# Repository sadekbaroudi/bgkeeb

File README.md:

# Pronunciation

Baby Groot Keyboard (bgkeeb)

This is a reversible 100mm x 100mm pcb with support for mx or choc switches (no hotswap), per key led, rotary encoders, and exposes the SDA/SCL/GND/VCC lines in the form of the pimoroni trackball pins (meaning you can add that as well, though the case doesn't support it, so you'll need to devise your own mechanism).

Given the pcb is so small, pcb prototype manufacturers will fab this for very cheap, or even free. As of this writing, nextpcb will ship fab and ship this keyboard 100% for free (in green only). jlcpcb will fab and ship these for $2 (USD).

# PCBs

There are two pcbs, the choc version and the mx version.

For the mx version, see the pcb/mx directory in the repository
For the choc version, see the pcb/mx directory in the repository

# Support me!

I have spent a lot of time and money designing prototypes, testing, developing, etc. Any contributions would be greatly appreciated!

If you don't want to, or can't afford to support me, please send me a message to let me know you've built one, along with pictures. Also, feel free to submit a pull request with pictures into this repository. I'd be happy to showcase your build.

Reddit: /u/sadekbaroudi
Discord: sadekbaroudi#1258

# Firmware

You can use the firmware found here:
https://github.com/sadekbaroudi/qmk_firmware/tree/master/keyboards/fingerpunch/bgkeeb/

zmk firmware here: https://github.com/ezxzeng/zmk-bgkeeb

# Pictures

# Submitted build pics

@ardakilic

@carboncopy101

@robopuff

@JulioPDX

@ezxzeng

case for the wireless choc build found [here](https://cad.onshape.com/documents/f9433f7cbaacd819773968dc/w/7cd753696df5795c5e7db3c3/e/7a6c60eb671b22fb31dd6c76)

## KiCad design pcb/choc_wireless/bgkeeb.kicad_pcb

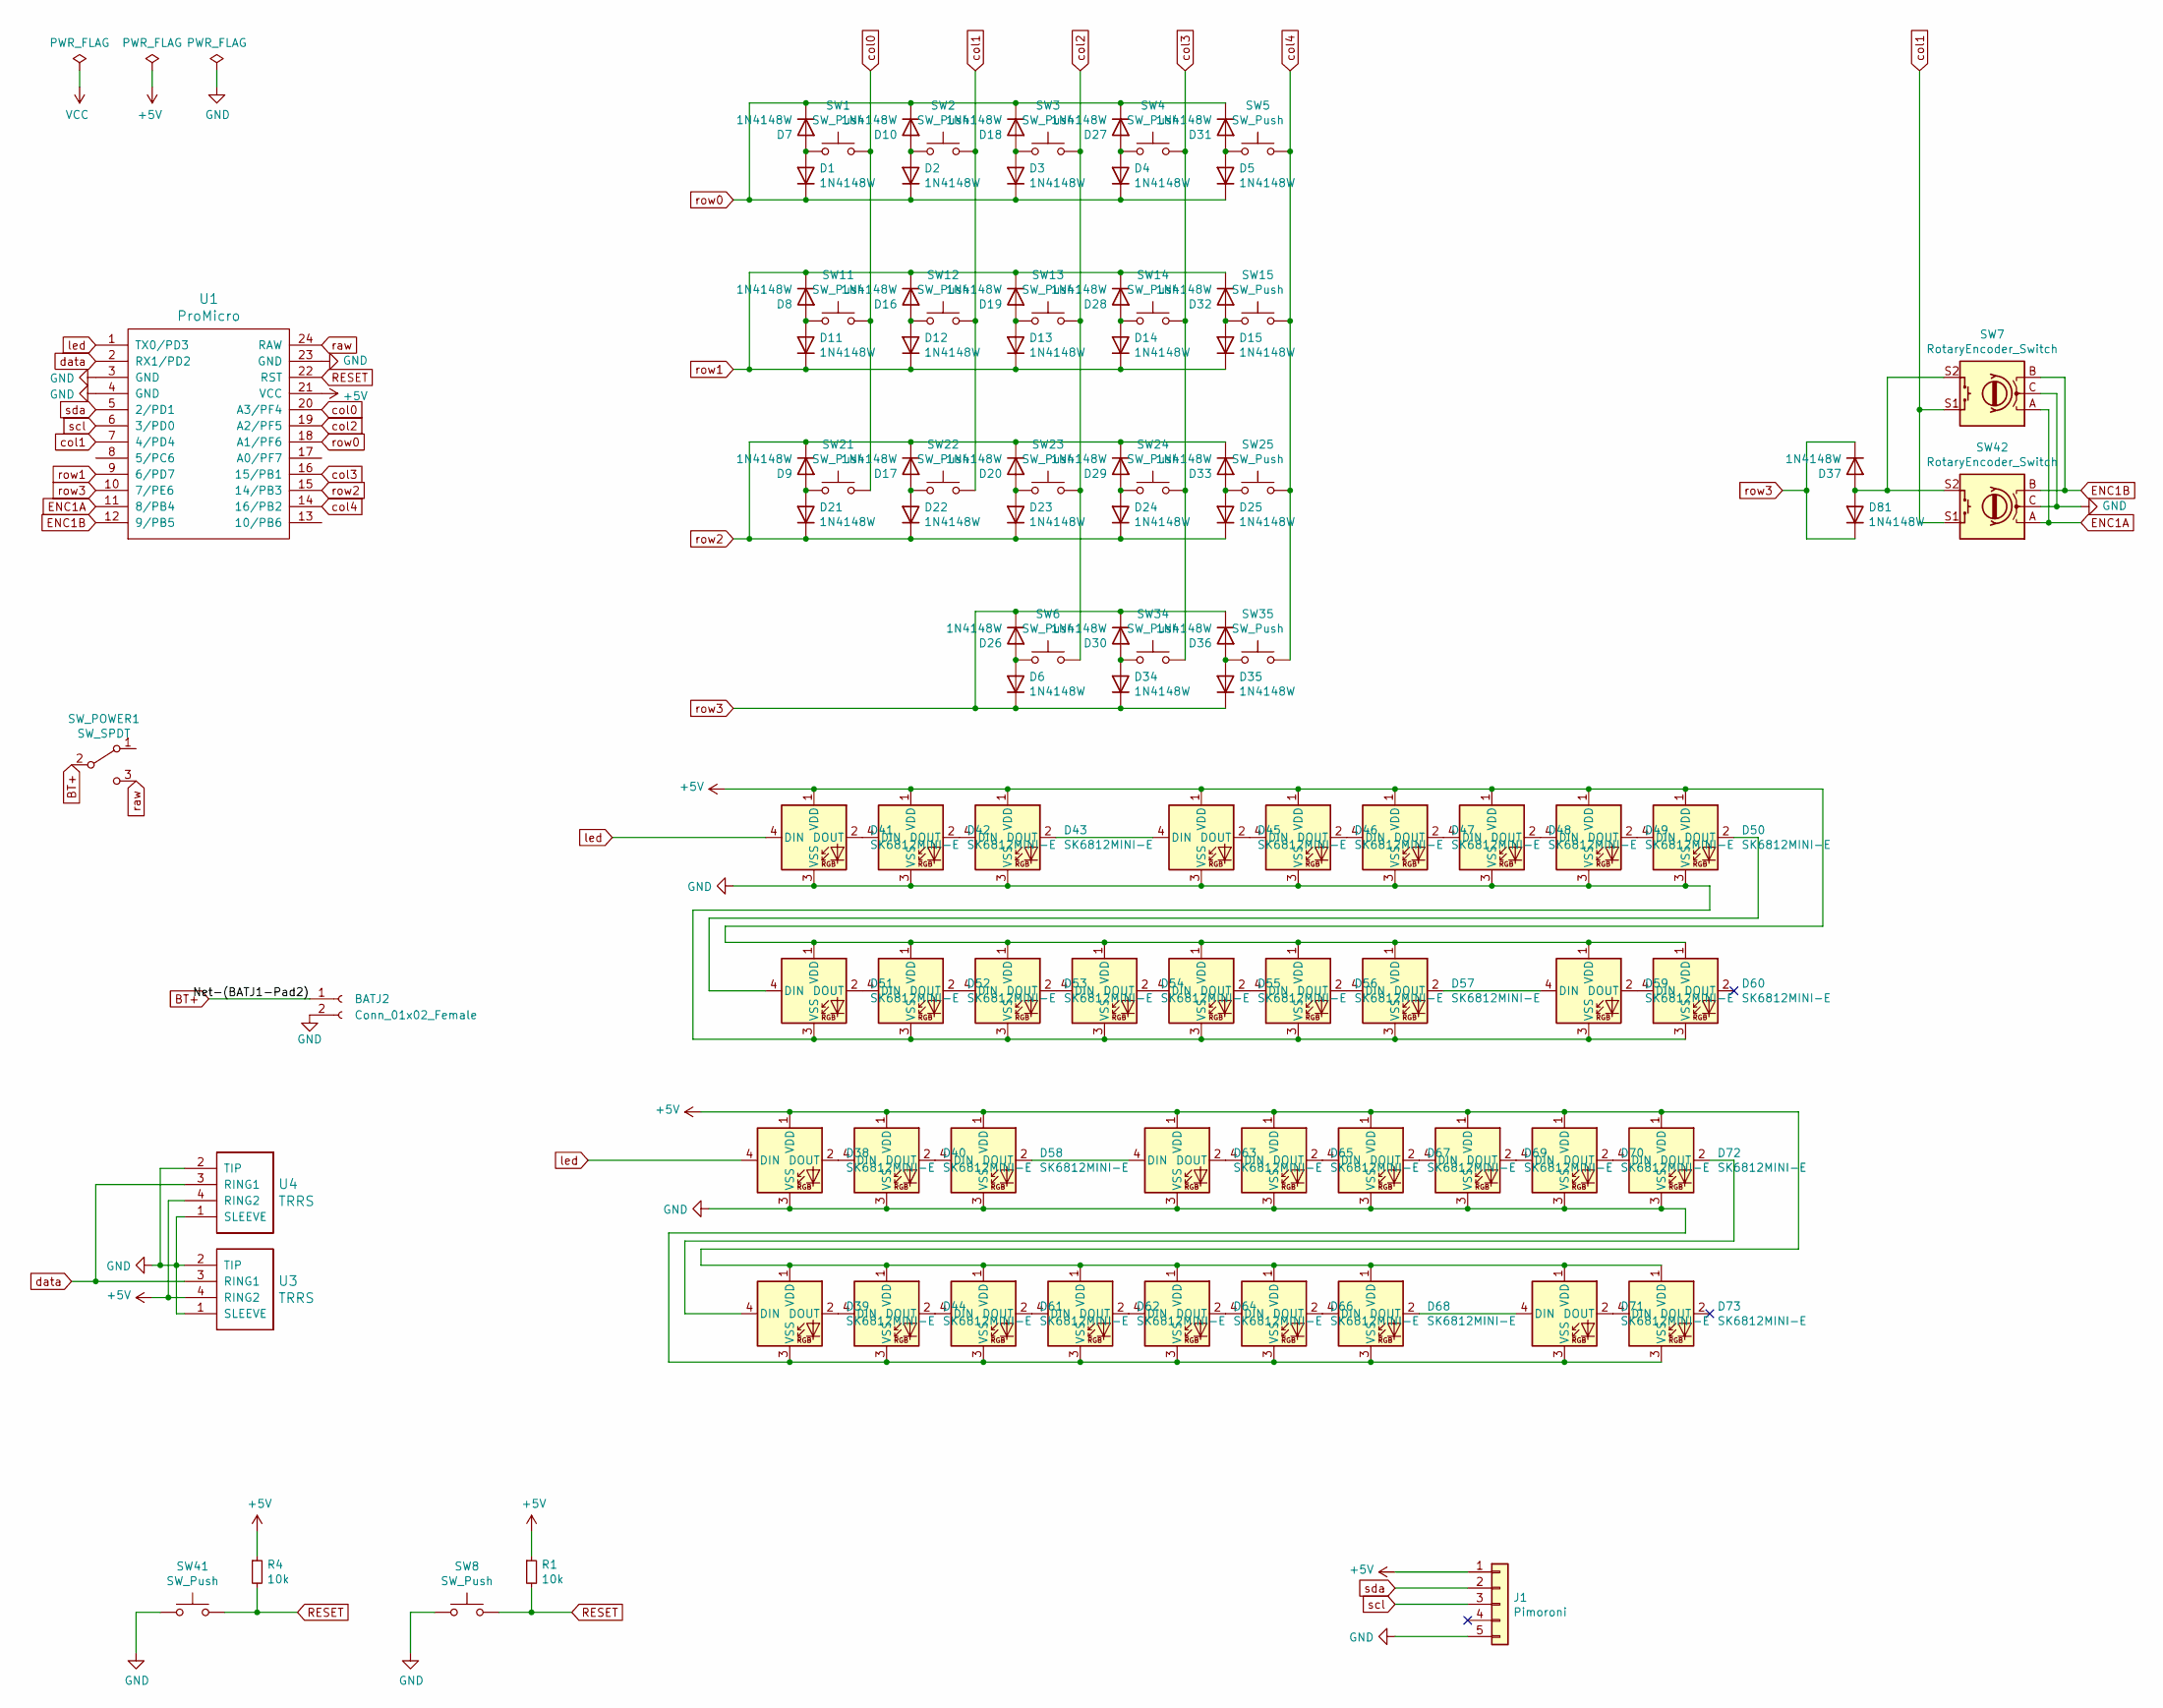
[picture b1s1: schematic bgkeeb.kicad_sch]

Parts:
BATJ2: Conn_01x02_Female; JST_PH_S2B-PH-K_1x02_P2.00mm_Horizontal_reversible
D1, D2, D3, D4, D5, D6, D7, D8, D9, D10, D11, D12, D13, D14, D15, D16, D17, D18, D19, D20, D21, D22, D23, D24, D25, D26, D27, D28, D29, D30, D31, D32, D33, D34, D35, D36, D37, D81: 1N4148W; D_SOD-123; LCSC C727110
D38, D39, D40, D41, D42, D43, D44, D45, D46, D47, D48, D49, D50, D51, D52, D53, D54, D55, D56, D57, D58, D59, D60, D61, D62, D63, D64, D65, D66, D67, D68, D69, D70, D71, D72, D73: SK6812MINI-E; MX_SK6812MINI-E
J1: Pimoroni; pimoroni
R1, R4: 10k; R_0805_2012Metric; LCSC C17414
SW1, SW2, SW3, SW4, SW5, SW6, SW11, SW12, SW13, SW14, SW15, SW21, SW22, SW23, SW24, SW25, SW34, SW35: SW_Push; SW_PG1350_reversible
SW7, SW42: RotaryEncoder_Switch; RotaryEncoder_EC11-no-legs
SW8, SW41: SW_Push; SKQG-1155865
SW_POWER1: SW_SPDT; SW_SPDT_PCM12_reversible
U1: ProMicro; ArduinoProMicro
U3, U4: TRRS; TRRS-PJ-320A

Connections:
+5V: D38.1 (VDD), D39.1 (VDD), D40.1 (VDD), D41.1 (VDD), D42.1 (VDD), D43.1 (VDD), D44.1 (VDD), D45.1 (VDD), D46.1 (VDD), D47.1 (VDD), D48.1 (VDD), D49.1 (VDD), D50.1 (VDD), D51.1 (VDD), D52.1 (VDD), D53.1 (VDD), D54.1 (VDD), D55.1 (VDD), D56.1 (VDD), D57.1 (VDD), D58.1 (VDD), D59.1 (VDD), D60.1 (VDD), D61.1 (VDD), D62.1 (VDD), D63.1 (VDD), D64.1 (VDD), D65.1 (VDD), D66.1 (VDD), D67.1 (VDD), D68.1 (VDD), D69.1 (VDD), D70.1 (VDD), D71.1 (VDD), D72.1 (VDD), D73.1 (VDD), J1.1, R1.1, R4.1, U1.21 (VCC), U3.4 (RING2), U4.4 (RING2)
BT+: SW_POWER1.2 (B); also elsewhere on the board
ENC1A: SW7.A, SW42.A, U1.11 (8/PB4)
ENC1B: SW7.B, SW42.B, U1.12 (9/PB5)
GND: D38.3 (VSS), D39.3 (VSS), D40.3 (VSS), D41.3 (VSS), D42.3 (VSS), D43.3 (VSS), D44.3 (VSS), D45.3 (VSS), D46.3 (VSS), D47.3 (VSS), D48.3 (VSS), D49.3 (VSS), D50.3 (VSS), D51.3 (VSS), D52.3 (VSS), D53.3 (VSS), D54.3 (VSS), D55.3 (VSS), D56.3 (VSS), D57.3 (VSS), D58.3 (VSS), D59.3 (VSS), D60.3 (VSS), D61.3 (VSS), D62.3 (VSS), D63.3 (VSS), D64.3 (VSS), D65.3 (VSS), D66.3 (VSS), D67.3 (VSS), D68.3 (VSS), D69.3 (VSS), D70.3 (VSS), D71.3 (VSS), D72.3 (VSS), D73.3 (VSS), J1.5, SW7.C, SW8.1, SW41.1, SW42.C, U1.3 (GND), U1.4 (GND), U1.23 (GND), U3.1 (SLEEVE), U3.2 (TIP), U4.1 (SLEEVE), U4.2 (TIP); also elsewhere on the board
unnamed: D1.2 (A), D7.2 (A), SW1.1
unnamed: D2.2 (A), D10.2 (A), SW2.1
unnamed: D8.2 (A), D11.2 (A), SW11.1
unnamed: D12.2 (A), D16.2 (A), SW12.1
unnamed: D13.2 (A), D19.2 (A), SW13.1
unnamed: D14.2 (A), D28.2 (A), SW14.1
unnamed: D15.2 (A), D32.2 (A), SW15.1
unnamed: D17.2 (A), D22.2 (A), SW22.1
unnamed: D3.2 (A), D18.2 (A), SW3.1
unnamed: D20.2 (A), D23.2 (A), SW23.1
unnamed: D9.2 (A), D21.2 (A), SW21.1
unnamed: D24.2 (A), D29.2 (A), SW24.1
unnamed: D25.2 (A), D33.2 (A), SW25.1
unnamed: D6.2 (A), D26.2 (A), SW6.1
unnamed: D4.2 (A), D27.2 (A), SW4.1
unnamed: D30.2 (A), D34.2 (A), SW34.1
unnamed: D5.2 (A), D31.2 (A), SW5.1
unnamed: D35.2 (A), D36.2 (A), SW35.1
unnamed: D37.2 (A), D81.2 (A), SW7.S2, SW42.S2
unnamed: D38.2 (DOUT), D40.4 (DIN)
unnamed: D39.4 (DIN), D72.2 (DOUT)
unnamed: D39.2 (DOUT), D44.4 (DIN)
unnamed: D40.2 (DOUT), D58.4 (DIN)
unnamed: D41.2 (DOUT), D42.4 (DIN)
unnamed: D42.2 (DOUT), D43.4 (DIN)
unnamed: D43.2 (DOUT), D45.4 (DIN)
unnamed: D44.2 (DOUT), D61.4 (DIN)
unnamed: D45.2 (DOUT), D46.4 (DIN)
unnamed: D46.2 (DOUT), D47.4 (DIN)
unnamed: D47.2 (DOUT), D48.4 (DIN)
unnamed: D48.2 (DOUT), D49.4 (DIN)
unnamed: D49.2 (DOUT), D50.4 (DIN)
unnamed: D50.2 (DOUT), D51.4 (DIN)
unnamed: D51.2 (DOUT), D52.4 (DIN)
unnamed: D52.2 (DOUT), D53.4 (DIN)
unnamed: D53.2 (DOUT), D54.4 (DIN)
unnamed: D54.2 (DOUT), D55.4 (DIN)
unnamed: D55.2 (DOUT), D56.4 (DIN)
unnamed: D56.2 (DOUT), D57.4 (DIN)
unnamed: D57.2 (DOUT), D59.4 (DIN)
unnamed: D58.2 (DOUT), D63.4 (DIN)
unnamed: D59.2 (DOUT), D60.4 (DIN)
unnamed: D61.2 (DOUT), D62.4 (DIN)
unnamed: D62.2 (DOUT), D64.4 (DIN)
unnamed: D63.2 (DOUT), D65.4 (DIN)
unnamed: D64.2 (DOUT), D66.4 (DIN)
unnamed: D65.2 (DOUT), D67.4 (DIN)
unnamed: D66.2 (DOUT), D68.4 (DIN)
unnamed: D67.2 (DOUT), D69.4 (DIN)
unnamed: D68.2 (DOUT), D71.4 (DIN)
unnamed: D69.2 (DOUT), D70.4 (DIN)
unnamed: D70.2 (DOUT), D72.4 (DIN)
unnamed: D71.2 (DOUT), D73.4 (DIN)
RESET: R1.2, R4.2, SW8.2, SW41.2, U1.22 (RST)
col0: SW1.2, SW11.2, SW21.2, U1.20 (A3/PF4)
col1: SW2.2, SW7.S1, SW12.2, SW22.2, SW42.S1, U1.7 (4/PD4)
col2: SW3.2, SW6.2, SW13.2, SW23.2, U1.19 (A2/PF5)
col3: SW4.2, SW14.2, SW24.2, SW34.2, U1.16 (15/PB1)
col4: SW5.2, SW15.2, SW25.2, SW35.2, U1.14 (16/PB2)
data: U1.2 (RX1/PD2), U3.3 (RING1), U4.3 (RING1)
led: D38.4 (DIN), D41.4 (DIN), U1.1 (TX0/PD3)
raw: SW_POWER1.3 (C), U1.24 (RAW)
row0: D1.1 (K), D2.1 (K), D3.1 (K), D4.1 (K), D5.1 (K), D7.1 (K), D10.1 (K), D18.1 (K), D27.1 (K), D31.1 (K), U1.18 (A1/PF6)
row1: D8.1 (K), D11.1 (K), D12.1 (K), D13.1 (K), D14.1 (K), D15.1 (K), D16.1 (K), D19.1 (K), D28.1 (K), D32.1 (K), U1.9 (6/PD7)
row2: D9.1 (K), D17.1 (K), D20.1 (K), D21.1 (K), D22.1 (K), D23.1 (K), D24.1 (K), D25.1 (K), D29.1 (K), D33.1 (K), U1.15 (14/PB3)
row3: D6.1 (K), D26.1 (K), D30.1 (K), D34.1 (K), D35.1 (K), D36.1 (K), D37.1 (K), D81.1 (K), U1.10 (7/PE6)
scl: J1.3, U1.6 (3/PD0)
sda: J1.2, U1.5 (2/PD1)

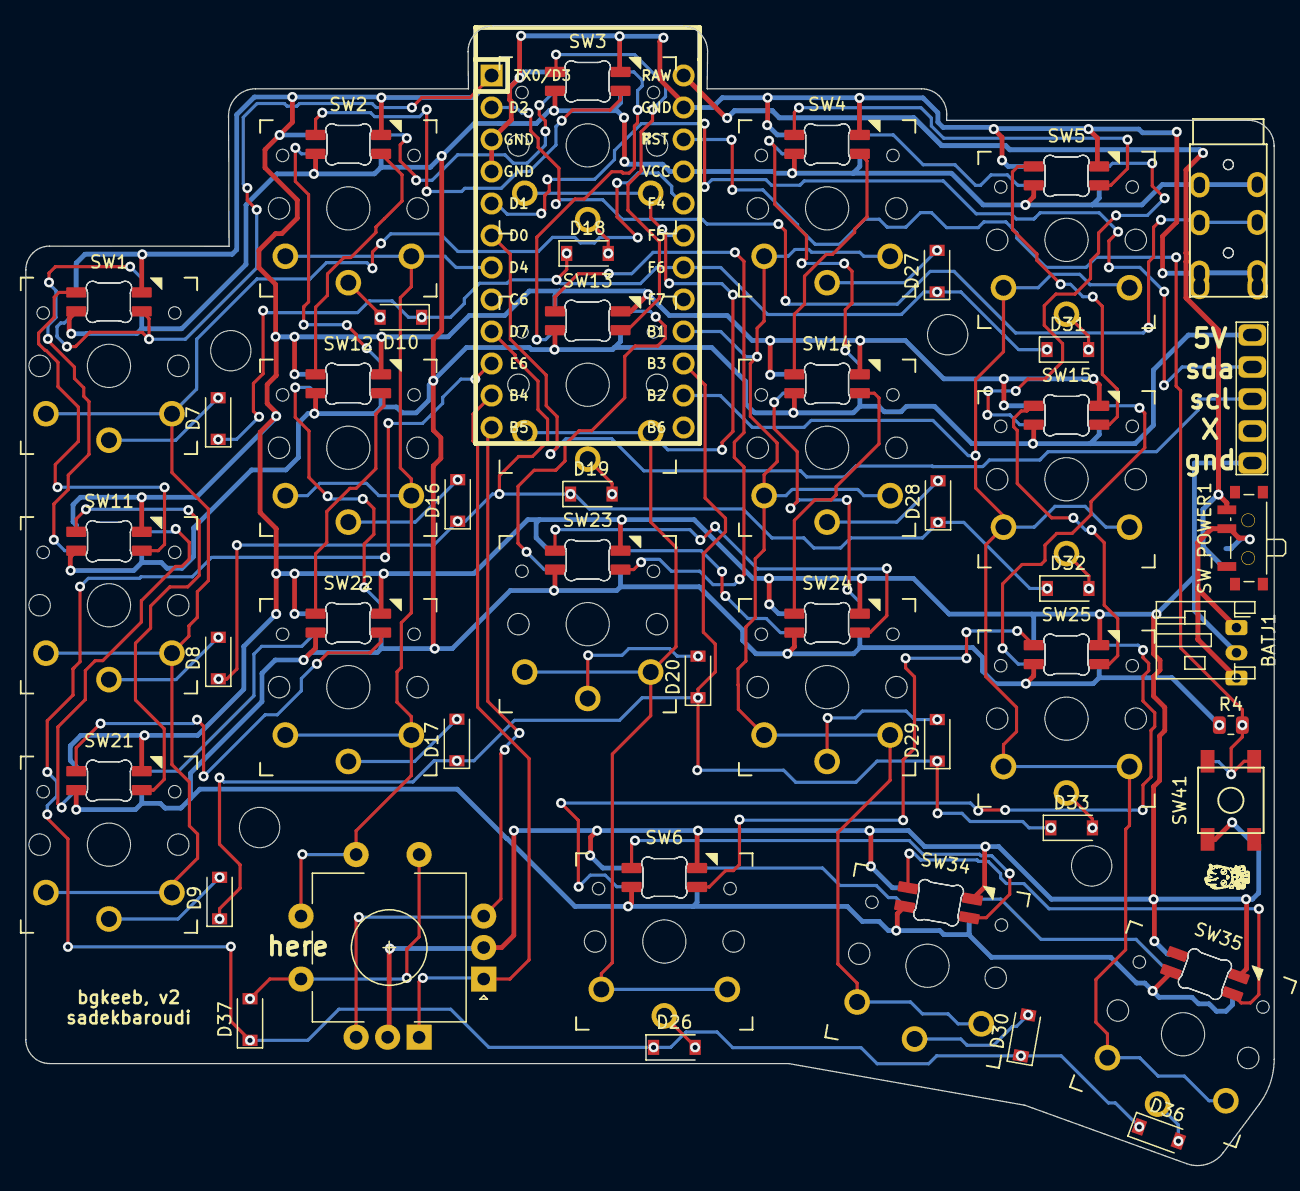
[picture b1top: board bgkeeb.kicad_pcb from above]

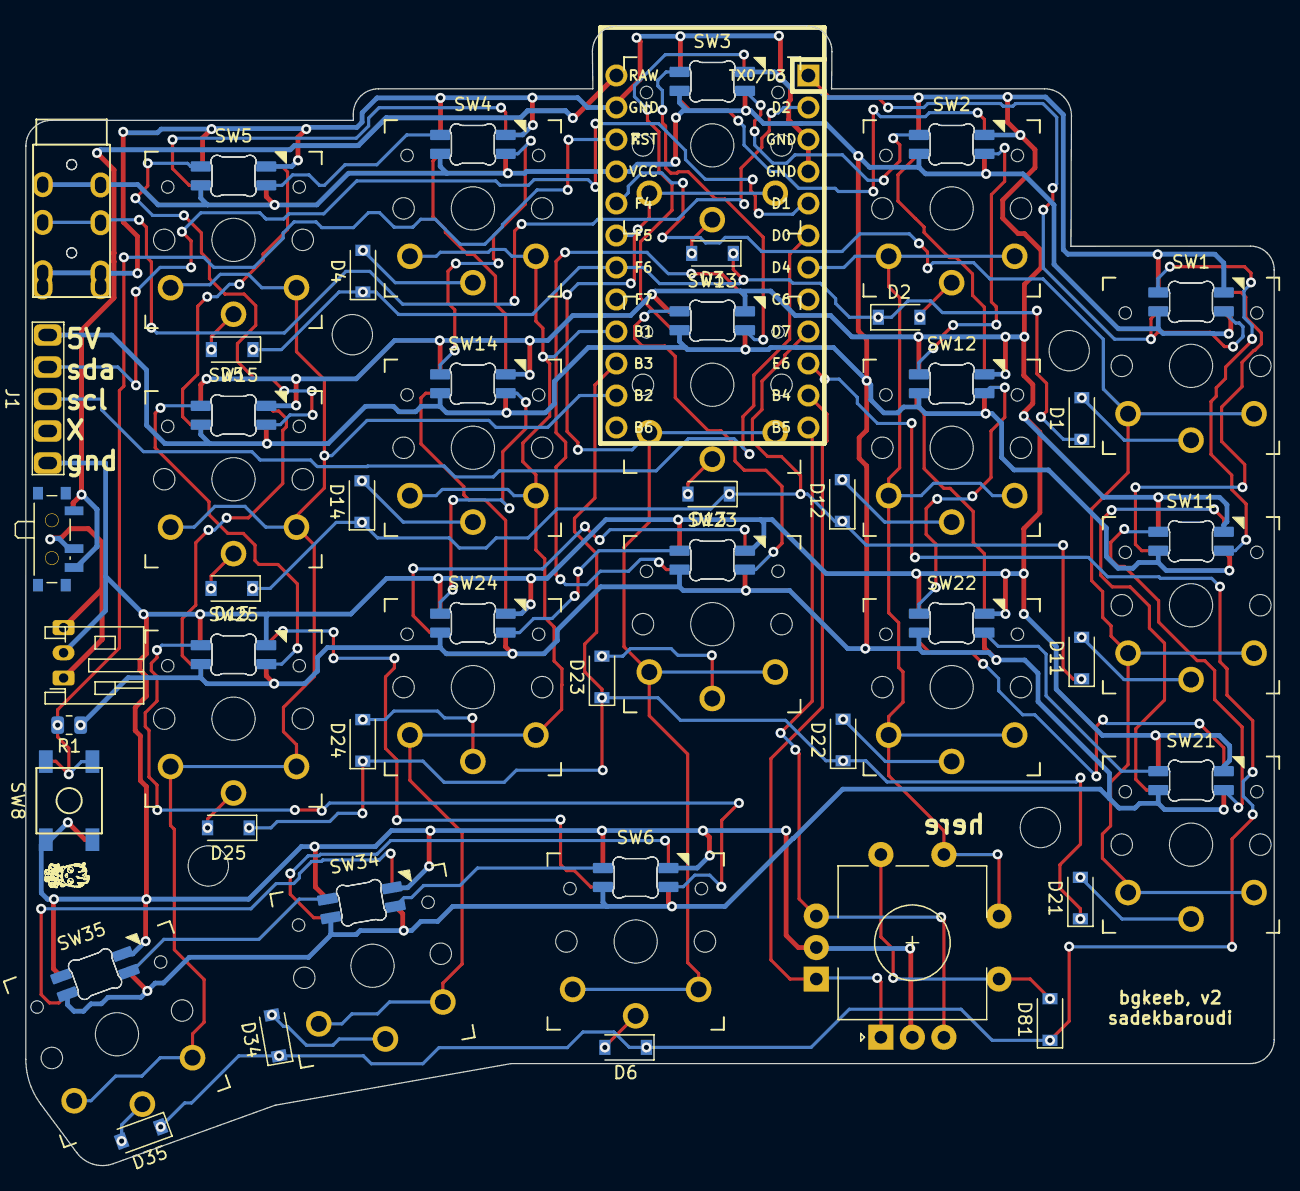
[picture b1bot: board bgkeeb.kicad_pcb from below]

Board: 2 copper layers, 99.1 x 90.5 mm, 104 parts (42 on the bottom side), 73 nets.

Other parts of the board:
BATJ1: Conn_01x02_Female; JST_PH_S2B-PH-K_1x02_P2.00mm_Horizontal_reversible

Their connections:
BT+: BATJ1.1; also elsewhere on the board
GND: BATJ1.2; also elsewhere on the board

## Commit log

2021-11-02 updated TRRS order
2021-11-02 removed old gerber files, fixed rotary encoder on the back
2021-11-02 Updated to add mounting holes
2021-11-04 case files for plate case
2021-11-04 added full body case
2021-11-04 aux jack wasn't wired, no functional impact, just got DRC errors
2021-11-05 wrong switch hole size
2021-11-08 the case was 1mm too small for the pcb, fixed
2021-11-09 fixed a lot of things
2021-11-19 build guide
2021-11-19 added EC11 covers
2021-11-24 build guide update and picture
2021-11-25 added image of pcbs
2021-11-25 added some text to describe the board
2021-11-26 updated BOM to include a couple of missing items, and readme to include firmware
2021-11-30 build guide had the wrong number of pro micros and resistors required
2021-11-30 updated build guide to include link to aliexpress, since it's cheaper
2021-11-30 updated paypal link to direct paypal instead of donation, since they take 29%
2021-12-02 v2 fixes the diode direction being flipped on the reverse side of the board
2021-12-02 fixed confusion with diode direction, as it turns out, it's not an issue
2021-12-03 added plate gerbers for those that don't want to 3d print a case
2021-12-03 added images and a readme for the plates
2021-12-03 missed a switch hole line in my last commit
2021-12-09 added notes around the encoder placement
2021-12-14 missing mounting holes in bottom plate
2022-01-13 updated firmware link to fingerpunch
2022-02-11 Issue 2: Clarify how to handle the large legs on rotary encoders
2022-02-16 user submitted build picture
2022-03-28 more build pic from robopuff
2022-10-10 added layout tester
2022-11-23 bgkeeb choc, work in progress
2022-11-23 choc bgkeeb is complete
2022-11-23 updated readme to describe the choc version
2022-11-23 added choc case, renamed original case to mx case
2022-11-23 ardakilic build pic
2023-05-15 Adding build pic by JulioPDX
2023-11-08 added wireless pcb
2023-11-08 added pics, readme
